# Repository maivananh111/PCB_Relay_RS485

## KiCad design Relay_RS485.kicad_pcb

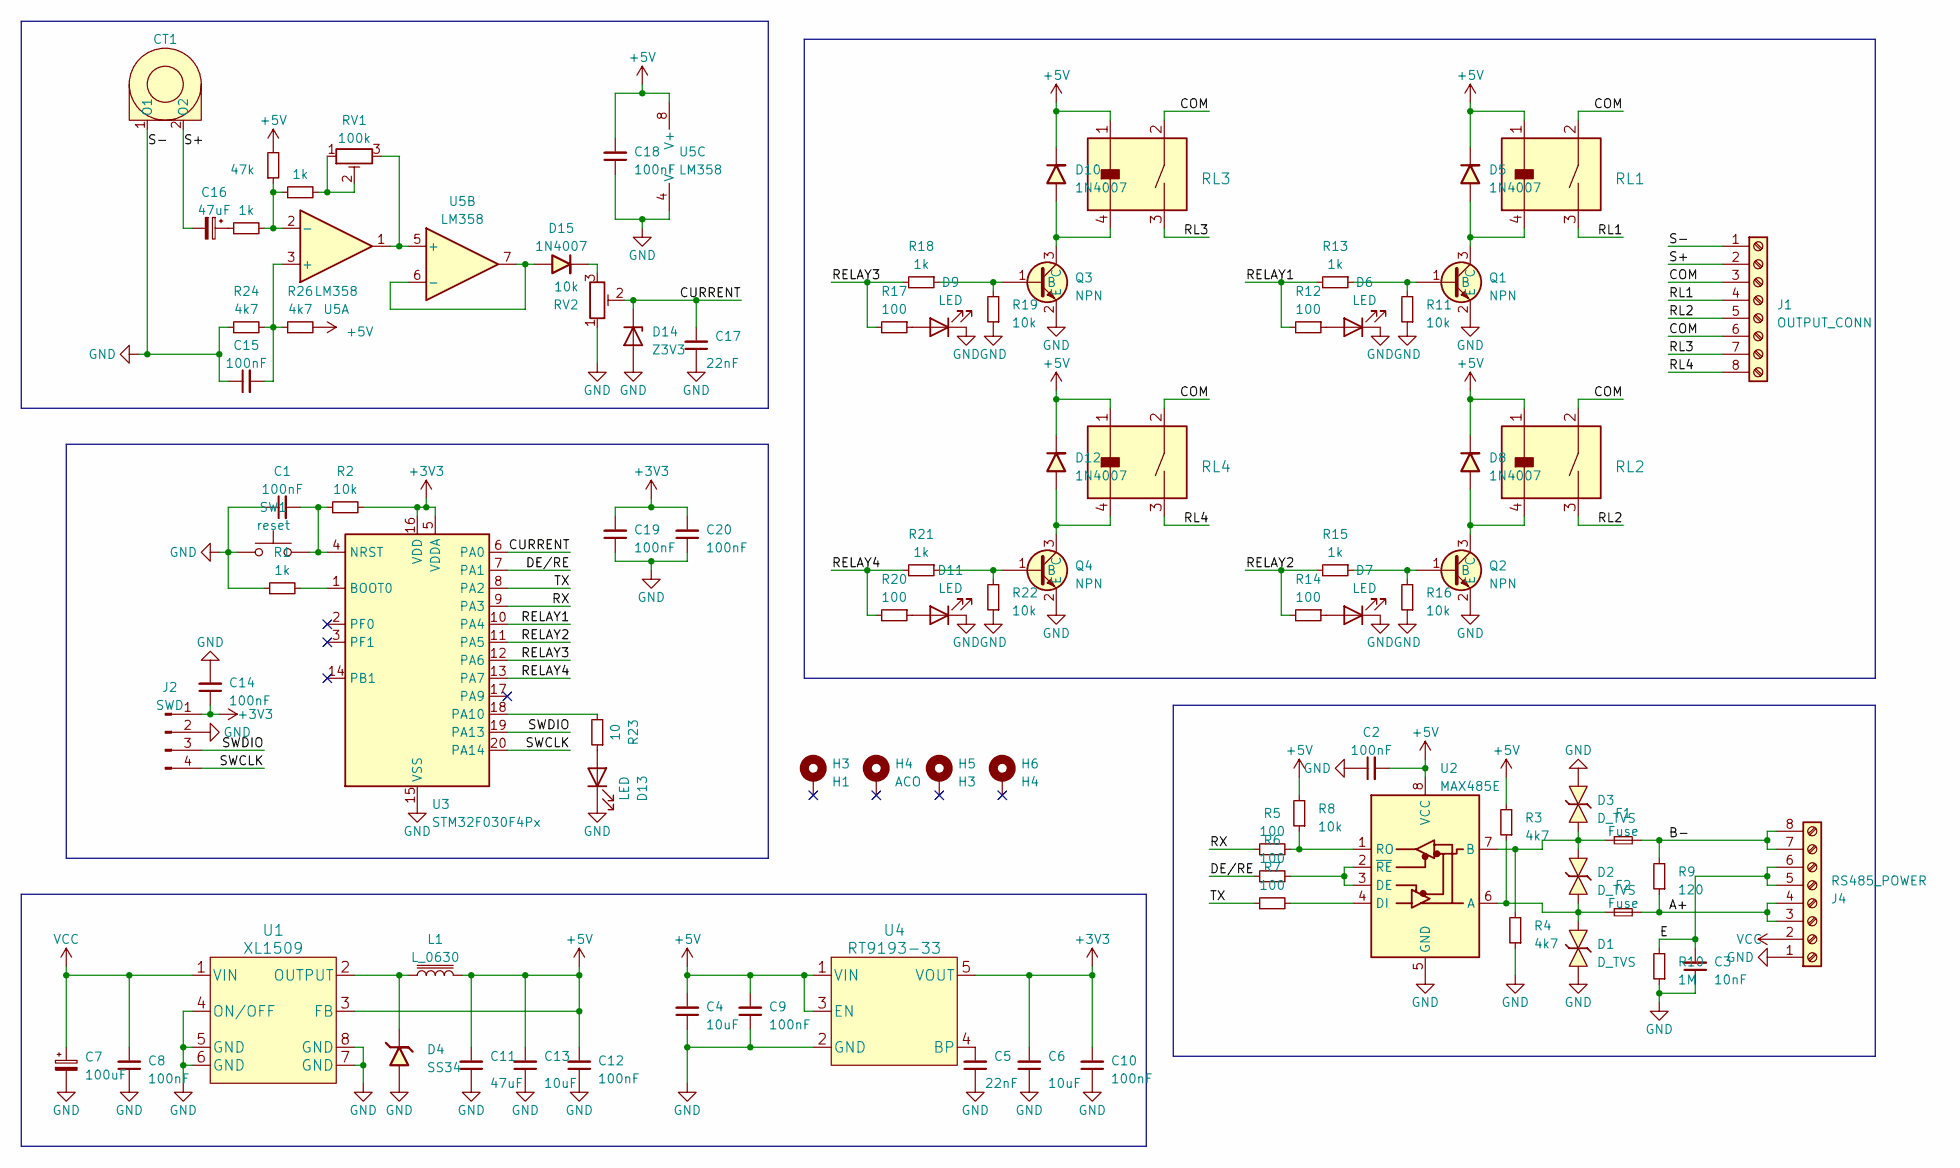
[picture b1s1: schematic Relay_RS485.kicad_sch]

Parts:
C1, C2, C8, C9, C10, C12, C14, C15, C18, C19, C20: 100nF; C_0603
C3: 10nF; C_0603
C4, C6, C13: 10uF; C_1210
C5, C17: 22nF; C_0603
C7: 100uF; CP_Elec_6.3x5.4_Nichicon
C11, C16: 47uF; C_1210
CT1: CurrentTransformer_THT
D1, D2, D3: D_TVS; D_SMA_TVS
D4: SS34; D_SMA
D5, D8, D10, D12, D15: 1N4007; SOD-123F
D6, D7, D9, D11, D13: LED; LED_0603
D14: Z3V3; D_MiniMELF
F1, F2: Fuse; F_1812
H3: H1; MountingHole_3.2mm_M3_Pad_Via
H4: ACO; MountingHole_3.2mm_M3_Pad_Via
H5: H3; MountingHole_3.2mm_M3_Pad_Via
H6: H4; MountingHole_3.2mm_M3_Pad_Via
J1: OUTPUT_CONN; TerminalBlock_Phoenix_MKDS-1,5-8-5.08_1x08_P5.08mm_Horizont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
J2: SWD; PinHeader_1x04_P2.54mm_Vertical
J4: RS485_POWER; TerminalBlock_Phoenix_MKDS-1,5-8-5.08_1x08_P5.08mm_Horizont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
L1: L_0630
Q1, Q2, Q3, Q4: NPN; SOT23-3
R1, R13, R15, R18, R21, R25, R27: 1k; R_0603
R2, R8, R11, R16, R19, R22: 10k; R_0603
R3, R4, R24, R26: 4k7; R_0603
R5, R6, R7, R12, R14, R17, R20: 100; R_0603
R9: 120; R_0805
R10: 1M; R_0603
R23: 10; R_0603
R28: 47k; R_0603
RL1, RL2, RL3, RL4: Relay_G5NB-1A-E_DC5; Relay_G5NB-1A-E DC5
RV1: 100k; Potentiometer_Bourns_3314J_Vertical
RV2: 10k; Potentiometer_Bourns_3314J_Vertical
SW1: reset; SW_SPST_CK_RS282G05A3
U1: XL1509; SOIC-8
U2: MAX485E; SOIC-8
U3: STM32F030F4Px; TSSOP-20_4.4x6.5mm_P0.65mm
U4: RT9193-33; SOT23-5
U5: LM358; SOIC-8

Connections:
+3V3: C6.2, C10.2, C14.1, C19.2, C20.2, J2.1, R2.2, U3.5 (VDDA), U3.16 (VDD), U4.5 (VOUT)
+5V: C2.2, C4.2, C9.2, C11.2, C12.2, C13.2, C18.2, D5.1, D8.1, D10.1, D12.1, L1.2, R3.2, R8.2, R26.2, R28.2, RL1.1, RL2.1, RL3.1, RL4.1, U1.3 (FB), U2.8 (VCC), U4.1 (VIN), U4.3 (EN), U5.8 (V+)
/A+: F2.2, J4.3, J4.4, R9.1
/B-: F1.2, J4.7, J4.8, R9.2
/COM: J1.3, J1.6, RL1.2, RL2.2, RL3.2, RL4.2
/CURRENT: C17.2, D14.1 (K), RV2.2, U3.6 (PA0)
/DE/RE: R6.1, U3.7 (PA1)
/E: C3.2, J4.5, J4.6, R10.2
/RELAY1: R12.2, R13.2, U3.10 (PA4)
/RELAY2: R14.2, R15.2, U3.11 (PA5)
/RELAY3: R17.2, R18.2, U3.12 (PA6)
/RELAY4: R20.2, R21.2, U3.13 (PA7)
/RL1: J1.4, RL1.3
/RL2: J1.5, RL2.3
/RL3: J1.7, RL3.3
/RL4: J1.8, RL4.3
/RX: R5.1, U3.9 (PA3)
/S+: C16.2, CT1.2 (O2), J1.2
/SWCLK: J2.4, U3.20 (PA14)
/SWDIO: J2.3, U3.19 (PA13)
/TX: R7.1, U3.8 (PA2)
GND: C1.1, C2.1, C3.1, C4.1, C5.1, C6.1, C7.2, C8.1, C9.1, C10.1, C11.1, C12.1, C13.1, C14.2, C15.1, C17.1, C18.1, C19.1, C20.1, CT1.1 (O1), D1.1 (A1), D3.2 (A2), D4.2, D6.1 (K), D7.1 (K), D9.1 (K), D11.1 (K), D13.1 (K), D14.2 (A), J1.1, J2.2, J4.1, Q1.2 (E), Q2.2 (E), Q3.2 (E), Q4.2 (E), R1.1, R4.1, R10.1, R11.1, R16.1, R19.1, R22.1, R24.1, RV2.1, SW1.1, U1.4 (ON/OFF), U1.5 (GND), U1.6 (GND), U1.7 (GND), U1.8 (GND), U2.5 (GND), U3.15 (VSS), U4.2 (GND), U5.4 (V-)
unnamed: C16.1, R25.1
unnamed: D1.2 (A2), D2.1 (A1), F2.1, R3.1, U2.6 (A)
unnamed: D2.2 (A2), D3.1 (A1), F1.1, R4.2, U2.7 (B)
unnamed: D6.2 (A), R12.1
unnamed: D7.2 (A), R14.1
unnamed: D9.2 (A), R17.1
unnamed: D11.2 (A), R20.1
unnamed: D13.2 (A), R23.1
unnamed: D15.1, RV2.3
unnamed: Q1.1 (B), R11.2, R13.1
unnamed: D5.2, Q1.3 (C), RL1.4
unnamed: Q2.1 (B), R15.1, R16.2
unnamed: D8.2, Q2.3 (C), RL2.4
unnamed: Q3.1 (B), R18.1, R19.2
unnamed: D10.2, Q3.3 (C), RL3.4
unnamed: Q4.1 (B), R21.1, R22.2
unnamed: D12.2, Q4.3 (C), RL4.4
unnamed: R27.2, RV1.1, RV1.2
unnamed: D4.1, L1.1, U1.2 (OUTPUT)
unnamed: R6.2, U2.2 (~RE), U2.3 (DE)
unnamed: R7.2, U2.4 (DI)
unnamed: R5.2, R8.1, U2.1 (RO)
unnamed: R1.2, U3.1 (BOOT0)
unnamed: C1.2, R2.1, SW1.2, U3.4 (NRST)
unnamed: R23.2, U3.18 (PA10)
unnamed: C5.2, U4.4 (BP)
unnamed: C15.2, R24.2, R26.1, U5.3 (+)
unnamed: R25.2, R27.1, R28.1, U5.2 (-)
unnamed: RV1.3, U5.1, U5.5 (+)
unnamed: D15.2, U5.6 (-), U5.7
VCC: C7.1, C8.2, J4.2, U1.1 (VIN)

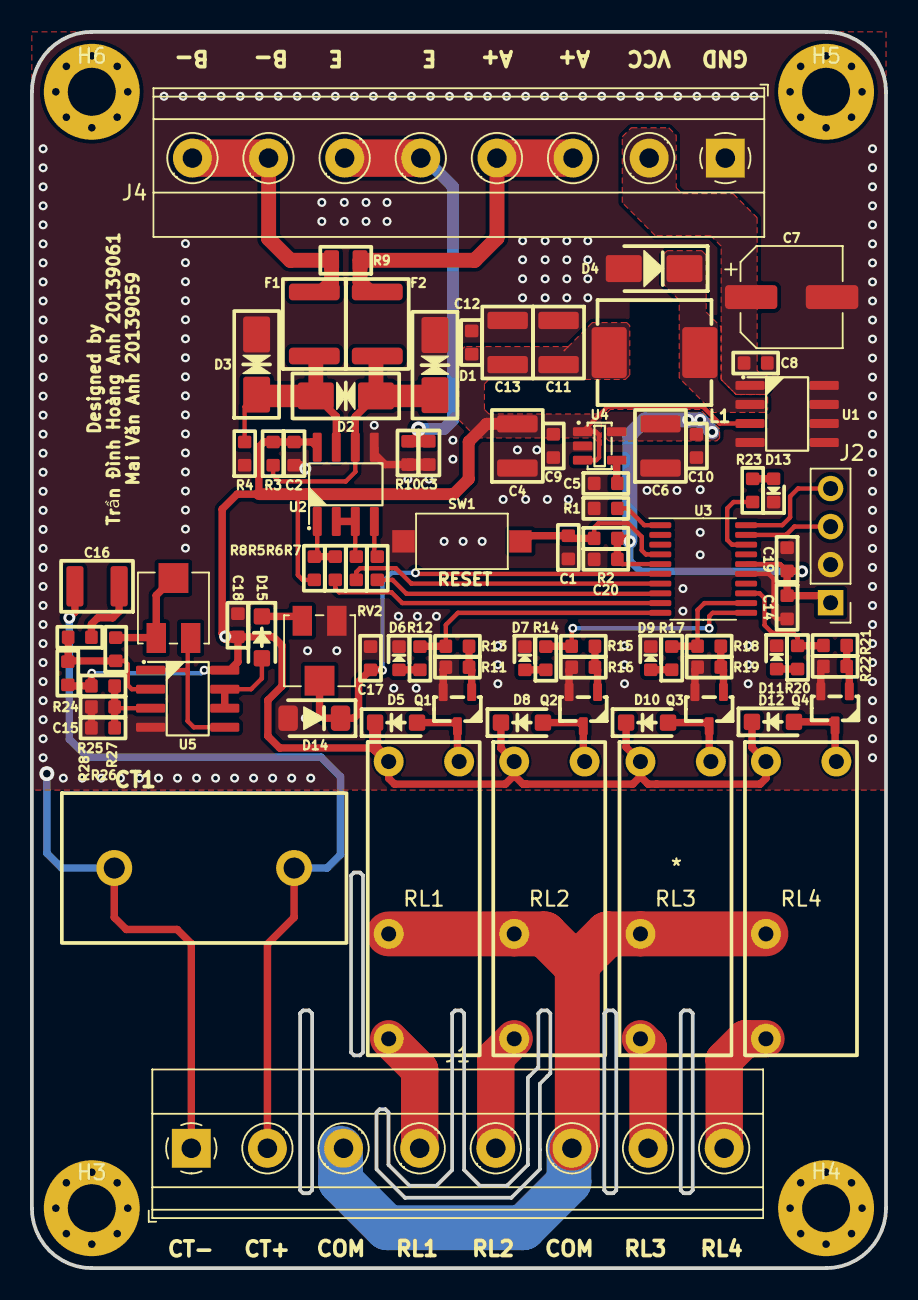
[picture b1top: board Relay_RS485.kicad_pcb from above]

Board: 2 copper layers, 57.0 x 82.5 mm, 90 parts (0 on the bottom side), 53 nets.

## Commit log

2023-04-14 Finish schematic.
2023-04-14 Finish board.

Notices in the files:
parts and their libraries:
Copyright 2021 Accelerated Designs. All rights reserved.
